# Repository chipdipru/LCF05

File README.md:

# LCF05
2nd Order L-C Output Filter for Class D amplifier
<p></p>
<p></p>

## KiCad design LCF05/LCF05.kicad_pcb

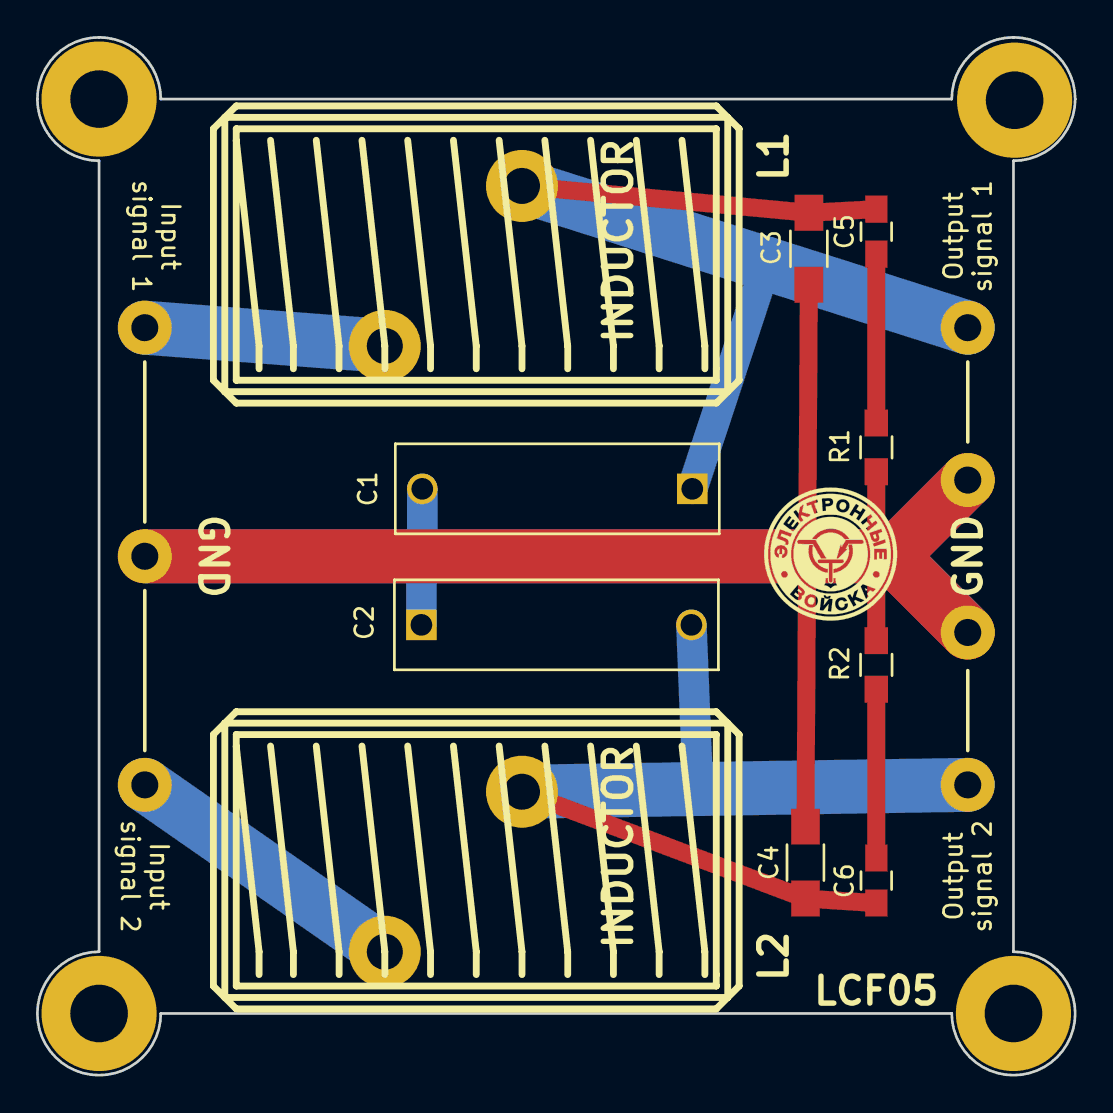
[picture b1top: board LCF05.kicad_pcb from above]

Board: 2 copper layers, 57.7 x 57.7 mm, 17 parts (0 on the bottom side), 7 nets.

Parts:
C1, C2: 0,47; C_Rect_L18_W5_P15
C3, C4: 1000p; C_1206_HandSoldering
C5, C6: 0,01; C_0805_HandSoldering
L1, L2: INDUCTOR; IND_ALTNC
P1, P2, P3, P4, P5, P6, P7: CONN_01X01; Measurement_Point_Round-TH_Big
R1, R2: 3R3; R_0805_HandSoldering

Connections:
GND: C1.2, C2.1, C3.2, C4.1, P2.1, P5.1, P6.1, R1.2, R2.1
unnamed: C1.1, C3.1, C5.1, L1.1, P4.1
unnamed: C2.2, C4.2, C6.2, L2.1, P7.1
unnamed: C5.2, R1.1
unnamed: C6.1, R2.2
unnamed: L1.2, P1.1
unnamed: L2.2, P3.1

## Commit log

2018-09-20 KiCad project
2018-09-20 schematic LCF05
2018-09-20 Gerber files
